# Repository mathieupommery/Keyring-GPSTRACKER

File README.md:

# Keyring-GPSTRACKER (v12.0)

<p align="center">
  <video src="https://github.com/user-attachments/assets/1a3d3f26-0a68-42e8-81eb-b6b98553143f" width="600" controls autoplay loop muted></video>
</p>

An ultra-compact, highly integrated modular GPS logger built around the STM32G0B1KE and a custom u-blox MIA-M10Q implementation. This project is designed as a fully functional, wearable GNSS tracker featuring worldwide offline geographical awareness, high-frequency SD card logging, Bluetooth connectivity, extreme power management (2µA shutdown draw), and modular waterproof enclosures.

## Key Features

* **Configurable High-Speed Logging:** Records tracks directly to the internal MicroSD card in `.GPX` or `.CSV` format. The logging frequency is adjustable, supporting real-time capture from **1Hz up to 10Hz**.
* **Worldwide Offline Awareness & Navigation:** Anywhere in the world, the device can instantly identify the closest city (name, direction, population) or the nearest mountain peak. It provides precise directional pointers by fusing data from the GPS, the MMC5603 compass, and the ICM-42688-P IMU.
* **Topological Barometer Calibration:** Future firmware implementation of an offline map of topological elevation points stored on the SD card, allowing ultra-precise, automatic recalibration of the barometer altitude.
* **BLE Smartphone Connectivity:** An external **DA14531 Bluetooth Low Energy (BLE)** module will handle seamless, low-power synchronization and configuration with a smartphone app.
* **Plug & Play USB:** Acts as a USB Mass Storage Class (MSC) over USB-C. Simply plug the tracker into a computer to access the MicroSD card and retrieve your tracks without removing the card.
* **Extreme Low Power:** Fully active power draw is around ~30mA. In shutdown mode, with only 1 LDO running for the STM32, the system draws just **2µA**.

---

## Modular Hardware Ecosystem (4 Custom PCBs)

The project relies on an ecosystem of four custom PCBs (two 6-layer boards and two 2-layer boards) connected via ultra-compact 5-pin board-to-board connectors.

### 1. Mainboard (6-Layer)
The core of the tracker, engineered to maximize available I/O ports while maintaining a tiny footprint.
* **MCU:** STM32G0B1KE (chosen for native USB FS 2.0, ultra-low power shutdown modes, and only 1 VDD pin).
* **Internal Sensors:** MMC5603 (compass), ICM-42688-P (IMU), and DPS368 (barometer).
* **Storage & Connectivity:** MicroSD card slot operating in SPI mode + external DA14531 BLE module support.
* **Power & Charging:** LTC4065 LiPo battery charger with USB-C connector.

#### BLE Expansion Module (DA14531)
To keep the mainboard ultra-compact while allowing wireless smartphone communication, wireless connectivity is offloaded to a dedicated mini extension PCB. Connected directly to the back of the mainboard via a board-to-board connector, this add-on integrates the ultra-low-power **Renesas DA14531 CodeLess BLE module**.

### 2. Custom GNSS Receiver Board (6-Layer)
A custom BGA adaptation of the u-blox **MIA-M10Q** receiver with a dedicated SAW filter and a top-mounted ceramic patch antenna. Designed as a footprint clone of the PA1010D, but utilizing a far superior engine capable of 10Hz updates across all constellations simultaneously.

### 3. Display & Waterproof Extension Panel (Breakaway 2-Layer PCB)

To optimize manufacturing, all auxiliary modules are designed as a single **snap-away (breakaway) panelized 2-layer PCB** so they can be produced together in one manufacturing run. Once snapped apart, the panel yields three distinct functional boards:

* **0.42" OLED Carrier Board:** Adapts a 0.42-inch SSD1306 OLED screen to the custom 5/6-pin board-to-board (B2B) connector format. It also breaks out the I2C bus to an external JST SM05B connector and includes an external GPIO breakout for a hardware button.
* **0.49" OLED Carrier Board:** Identical architecture to the 0.42" version (B2B adaptation, JST SM05B I2C breakout, button GPIO), but specifically dimensioned to mount a slightly larger 0.49-inch SSD1306 OLED screen.
* **Waterproof Dive Extension Board:** Designed specifically to mount inside the waterproof enclosure for deep-water excursions. It adds a **TE Connectivity 30-bar external pressure sensor** (effectively turning the tracker into a compact dive computer) and a magnetic **Hall-effect switch** for contactless power/stop-mode toggling through the solid sealed case.

## Smart Power Architecture

Power is cleanly isolated and distributed via 3 independent ultra-low IQ LDOs, controlled by the MCU:
* **LDO 1 (Always-on / MCU baseline):** Powers the STM32 directly. Responsible for the 2µA deep shutdown consumption.
* **LDO 2 (Switched):** Dedicated exclusively to the GNSS module.
* **LDO 3 (Switched):** Powers the SSD1306 display, the MicroSD card, external sensors (including the BLE module), and internal sensors.

---

## Enclosure System: Standard vs. Waterproof (Dive Mode)

The tracker features a modular, tool-free swap enclosure system depending on your activity:

### 1. Standard Compact Case
The daily-use enclosure. It is ultra-compact, non-waterproof, and provides direct access to the OLED display, physical buttons, MicroSD card slot, and USB-C port for charging and mass-storage data transfer.

### 2. Waterproof Dive Case
Similar to a GoPro housing, this heavy-duty case is designed for underwater excursions down to several hundred meters. 
* **How it works:** You remove the mainboard from the standard case, connect it to the **Waterproof Extension Board** (with the 30-bar sensor and Hall switch already mounted inside the dive case), turn it on, and seal the enclosure.
* **Note:** While in this temporary dive case, USB charging and physical MicroSD card access are blocked to ensure 100% water tightness. Power state is managed entirely through the external magnetic Hall sensor.

---

## Open Source

This project is fully open source! Feel free to explore the schematics, layouts, and firmware. If you find this project interesting or build your own, **please consider leaving a ⭐ on the repository!**

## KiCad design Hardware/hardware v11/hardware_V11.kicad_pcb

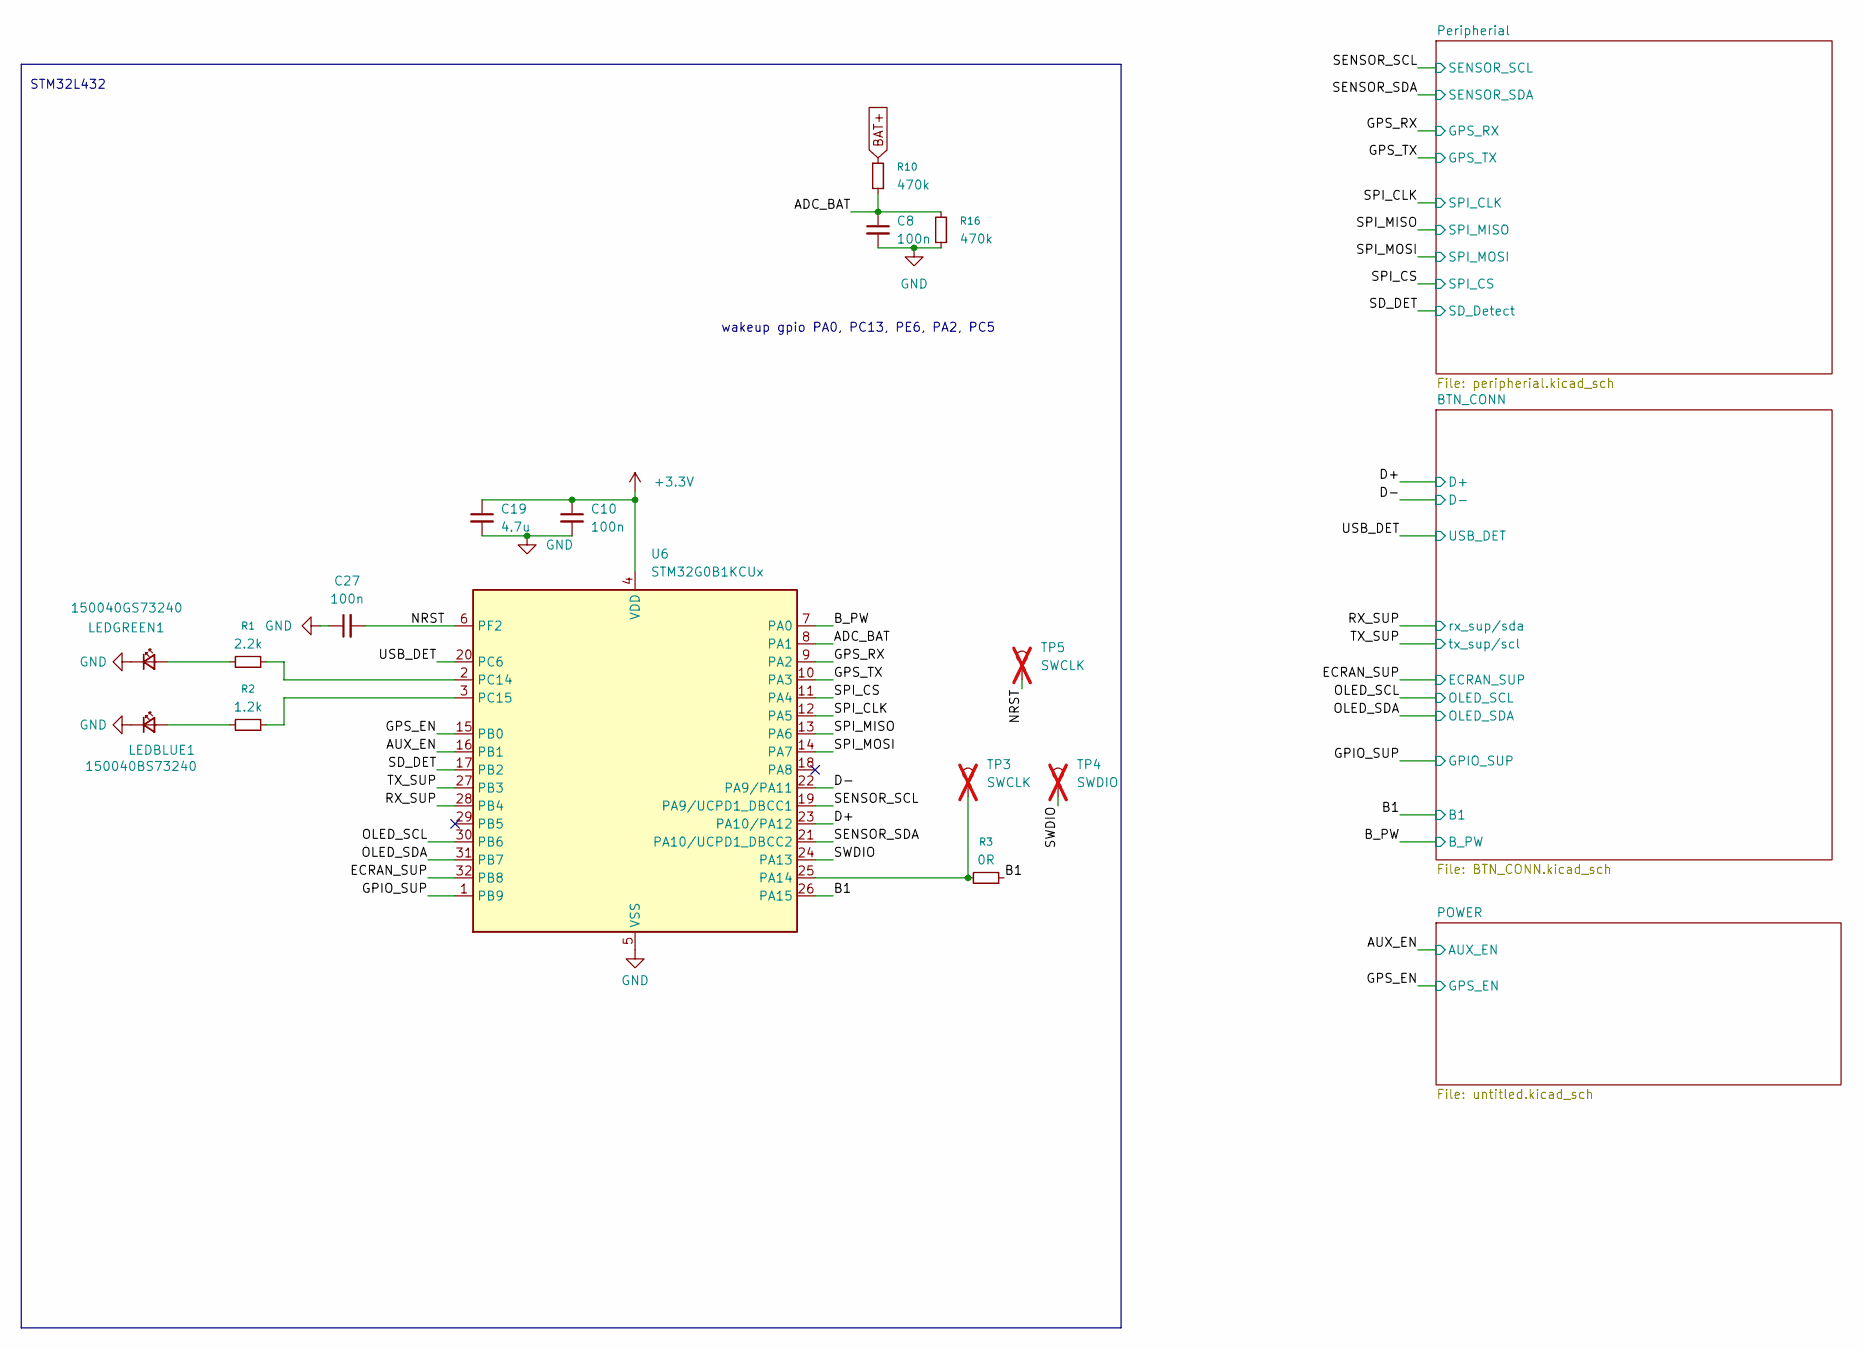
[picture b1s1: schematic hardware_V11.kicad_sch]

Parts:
C8, C10, C27: 100n; C_0201_0603Metric_Pad0.64x0.40mm_HandSolder
C19: 4.7u; C_0402_1005Metric
LEDBLUE1: 150040BS73240; LED_0402_1005Metric; Manufacturer_Part_Number 150040BS73240; Mouser Part Number 710-150040BS73240
LEDGREEN1: 150040GS73240; LED_0402_1005Metric; Manufacturer_Part_Number 150040GS73240; Mouser Part Number 710-150040GS73240
R1: 2.2k; R_0201_0603Metric_Pad0.64x0.40mm_HandSolder; Mouser Part Number 603-RC0201JR-07510RL
R2: 1.2k; R_0201_0603Metric_Pad0.64x0.40mm_HandSolder; Mouser Part Number 603-RC0201JR-07510RL
R3: 0R; R_0201_0603Metric_Pad0.64x0.40mm_HandSolder; Mouser Part Number 603-RC0201JR-07510RL
R10, R16: 470k; R_0201_0603Metric_Pad0.64x0.40mm_HandSolder; Mouser Part Number 603-AC0201FR-07470KL
TP3, TP5: SWCLK; pad_0.7mm; not fitted
TP4: SWDIO; pad_0.7mm; not fitted
U6: STM32G0B1KCUx; QFN-32-1EP_5x5mm_P0.5mm_EP3.45x3.45mm

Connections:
+3.3V: C10.1, C19.1, U6.4 (VDD); also elsewhere on the board
/ADC_BAT: C8.1, R10.2, R16.2, U6.8 (PA1)
/AUX_EN: U6.16 (PB1); also elsewhere on the board
/B1: R3.1, U6.26 (PA15); also elsewhere on the board
/B_PW: U6.7 (PA0); also elsewhere on the board
/D+: U6.23 (PA10/PA12); also elsewhere on the board
/D-: U6.22 (PA9/PA11); also elsewhere on the board
/ECRAN_SUP: U6.32 (PB8); also elsewhere on the board
/GPIO_SUP: U6.1 (PB9); also elsewhere on the board
/GPS_EN: U6.15 (PB0); also elsewhere on the board
/GPS_RX: U6.9 (PA2); also elsewhere on the board
/GPS_TX: U6.10 (PA3); also elsewhere on the board
/NRST: C27.2, TP5.1 (1_1), U6.6 (PF2)
/OLED_SCL: U6.30 (PB6); also elsewhere on the board
/OLED_SDA: U6.31 (PB7); also elsewhere on the board
/RX_SUP: U6.28 (PB4); also elsewhere on the board
/SD_DET: U6.17 (PB2); also elsewhere on the board
/SENSOR_SCL: U6.19 (PA9/UCPD1_DBCC1); also elsewhere on the board
/SENSOR_SDA: U6.21 (PA10/UCPD1_DBCC2); also elsewhere on the board
/SPI_CLK: U6.12 (PA5); also elsewhere on the board
/SPI_CS: U6.11 (PA4); also elsewhere on the board
/SPI_MISO: U6.13 (PA6); also elsewhere on the board
/SPI_MOSI: U6.14 (PA7); also elsewhere on the board
/SWDIO: TP4.1 (1_1), U6.24 (PA13)
/TX_SUP: U6.27 (PB3); also elsewhere on the board
/USB_DET: U6.20 (PC6); also elsewhere on the board
BAT+: R10.1; also elsewhere on the board
GND: C8.2, C10.2, C19.2, C27.1, LEDBLUE1.1 (K), LEDGREEN1.1 (K), R16.1, U6.5 (VSS), U6.33 (VSS); also elsewhere on the board
unnamed: LEDBLUE1.2 (A), R2.2
unnamed: LEDGREEN1.2 (A), R1.2
unnamed: R3.2, TP3.1 (1_1), U6.25 (PA14)
unnamed: R1.1, U6.2 (PC14)
unnamed: R2.1, U6.3 (PC15)

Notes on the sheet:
STM32L432
wakeup gpio PA0, PC13, PE6, PA2, PC5

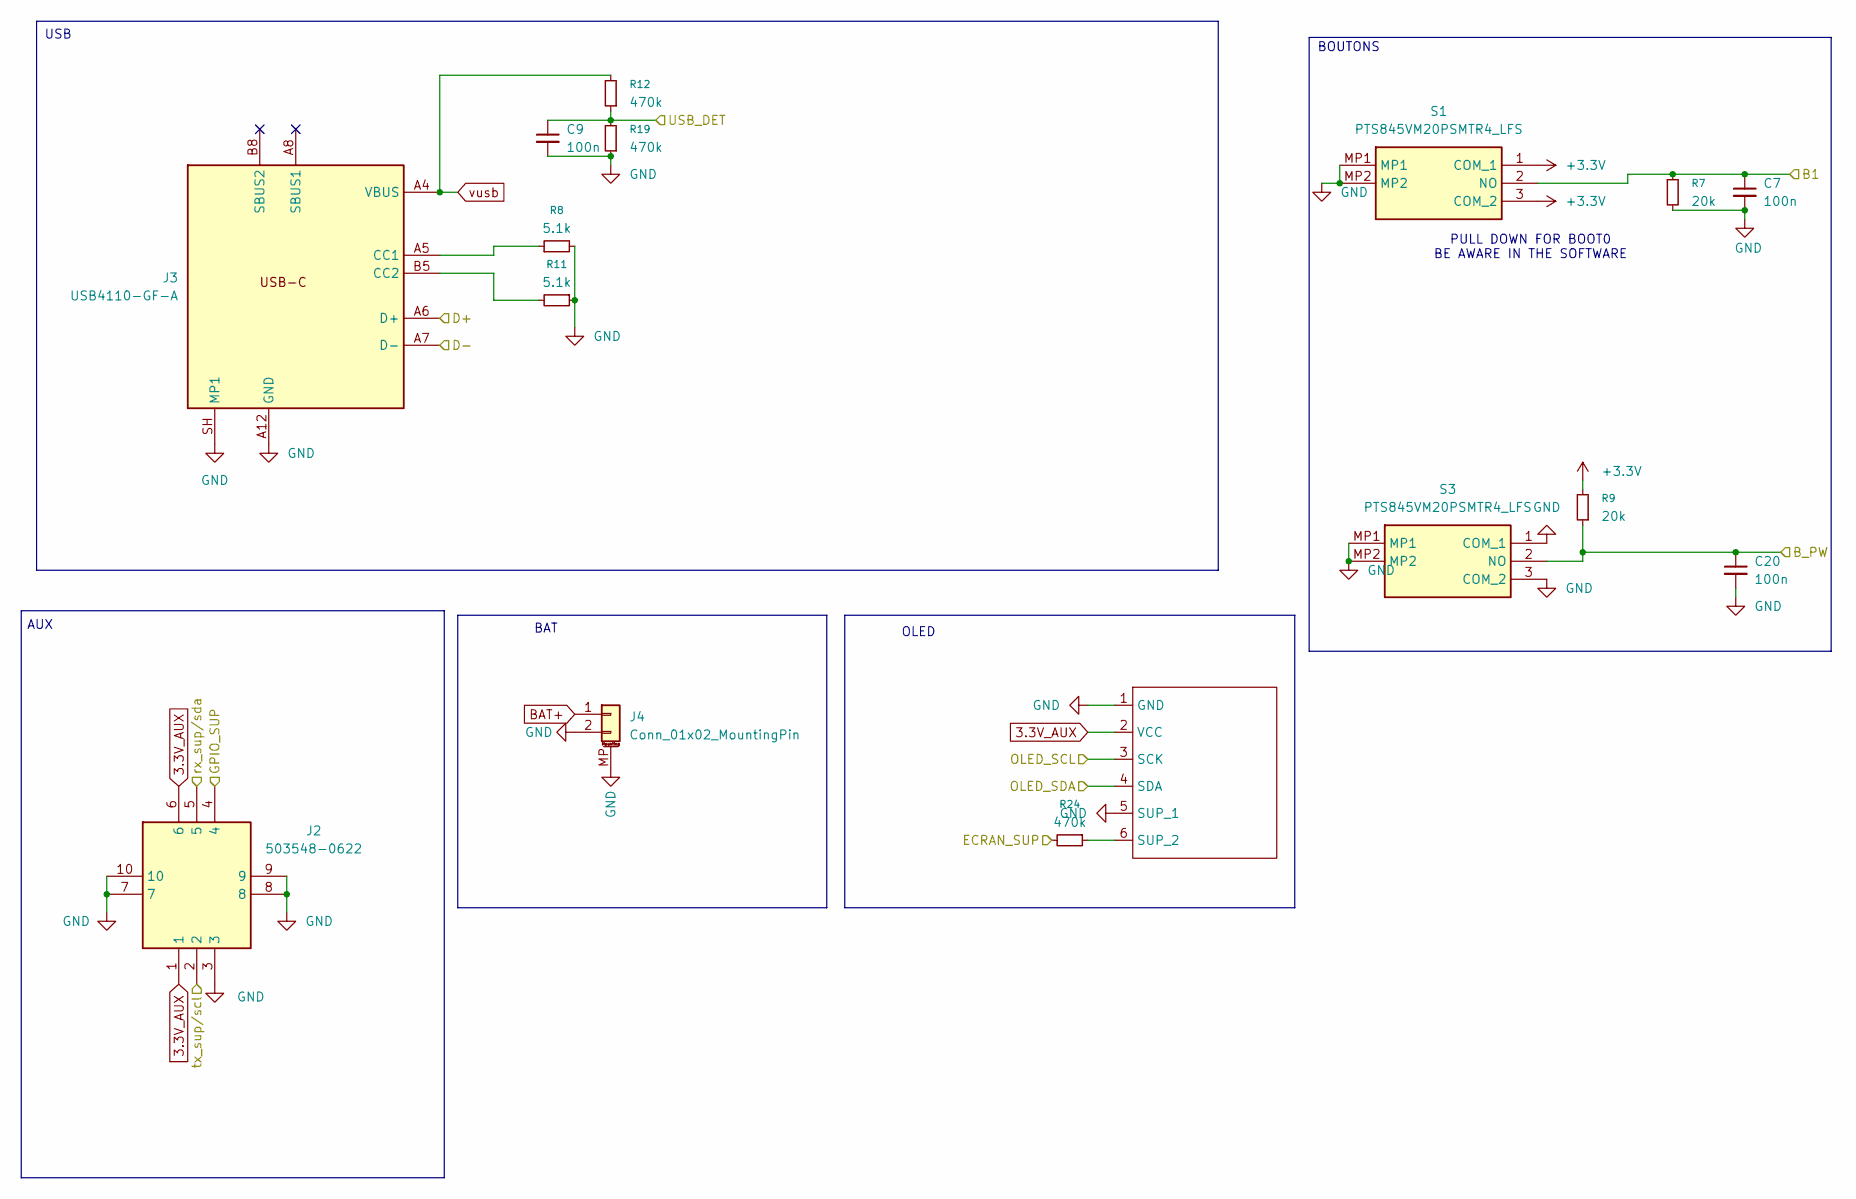
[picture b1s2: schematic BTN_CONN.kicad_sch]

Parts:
C7, C9, C20: 100n; C_0201_0603Metric_Pad0.64x0.40mm_HandSolder
J2: 503548-0622; 5035480622; Manufacturer_Part_Number 503548-0622; Mouser Part Number 538-503548-0622
J3: USB4110-GF-A; USB_C_Receptacle_GCT_USB4105-xx-A_16P_TopMnt_Horizontal; Mouser Part Number 640-USB4110-GF-A
J4: Conn_01x02_MountingPin; JST_SUR_BM02B-SURS-TF_1x02-1MP_P0.80mm_Vertical
R7, R9: 20k; R_0201_0603Metric_Pad0.64x0.40mm_HandSolder; Mouser Part Number 603-AC0201FR-0720KL
R8, R11: 5.1k; R_0201_0603Metric_Pad0.64x0.40mm_HandSolder; Mouser Part Number 603-AC0201FR-0720KL
R12, R19, R24: 470k; R_0201_0603Metric_Pad0.64x0.40mm_HandSolder; Mouser Part Number 603-AC0201FR-0720KL
S1, S3: PTS845VM20PSMTR4_LFS; PTS845VM20PSMTR4LFS; Manufacturer_Part_Number PTS845VM20PSMTR4 LFS; Mouser Part Number 611-PTS845VM20PSMTR4
U4: ssd1306_5point

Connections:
3.3V_AUX: J2.1, J2.6, U4.2 (VCC); also elsewhere on the board
+3.3V: R9.2, S1.1 (COM_1), S1.3 (COM_2); also elsewhere on the board
/B1: C7.1, R7.1, S1.2 (NO); also elsewhere on the board
/B_PW: C20.1, R9.1, S3.2 (NO); also elsewhere on the board
/D+: J3.A6 (D+), J3.B6 (D+); also elsewhere on the board
/D-: J3.A7 (D-), J3.B7 (D-); also elsewhere on the board
/ECRAN_SUP: R24.2; also elsewhere on the board
/GPIO_SUP: J2.4; also elsewhere on the board
/OLED_SCL: U4.3 (SCK); also elsewhere on the board
/OLED_SDA: U4.4 (SDA); also elsewhere on the board
/RX_SUP: J2.5; also elsewhere on the board
/TX_SUP: J2.2; also elsewhere on the board
/USB_DET: C9.1, R12.1, R19.2; also elsewhere on the board
BAT+: J4.1; also elsewhere on the board
GND: C7.2, C9.2, C20.2, J2.3, J2.7, J2.8, J2.9, J2.10, J3.A1 (GND), J3.A12 (GND), J3.B1 (GND), J3.B12 (GND), J3.SH (MP1), J4.2, J4.MP (MountPin), R7.2, R8.2, R11.1, R19.1, S1.MP1, S1.MP2, S3.1 (COM_1), S3.3 (COM_2), S3.MP1, S3.MP2, U4.1 (GND), U4.5 (SUP_1); also elsewhere on the board
unnamed: J3.A5 (CC1), R8.1
unnamed: J3.B5 (CC2), R11.2
unnamed: R24.1, U4.6 (SUP_2)
vusb: J3.A4 (VBUS), J3.A9 (VBUS), J3.B4 (VBUS), J3.B9 (VBUS), R12.2; also elsewhere on the board

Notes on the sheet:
AUX
BOUTONS
USB
PULL DOWN FOR BOOT0 BE AWARE IN THE SOFTWARE
OLED
BAT

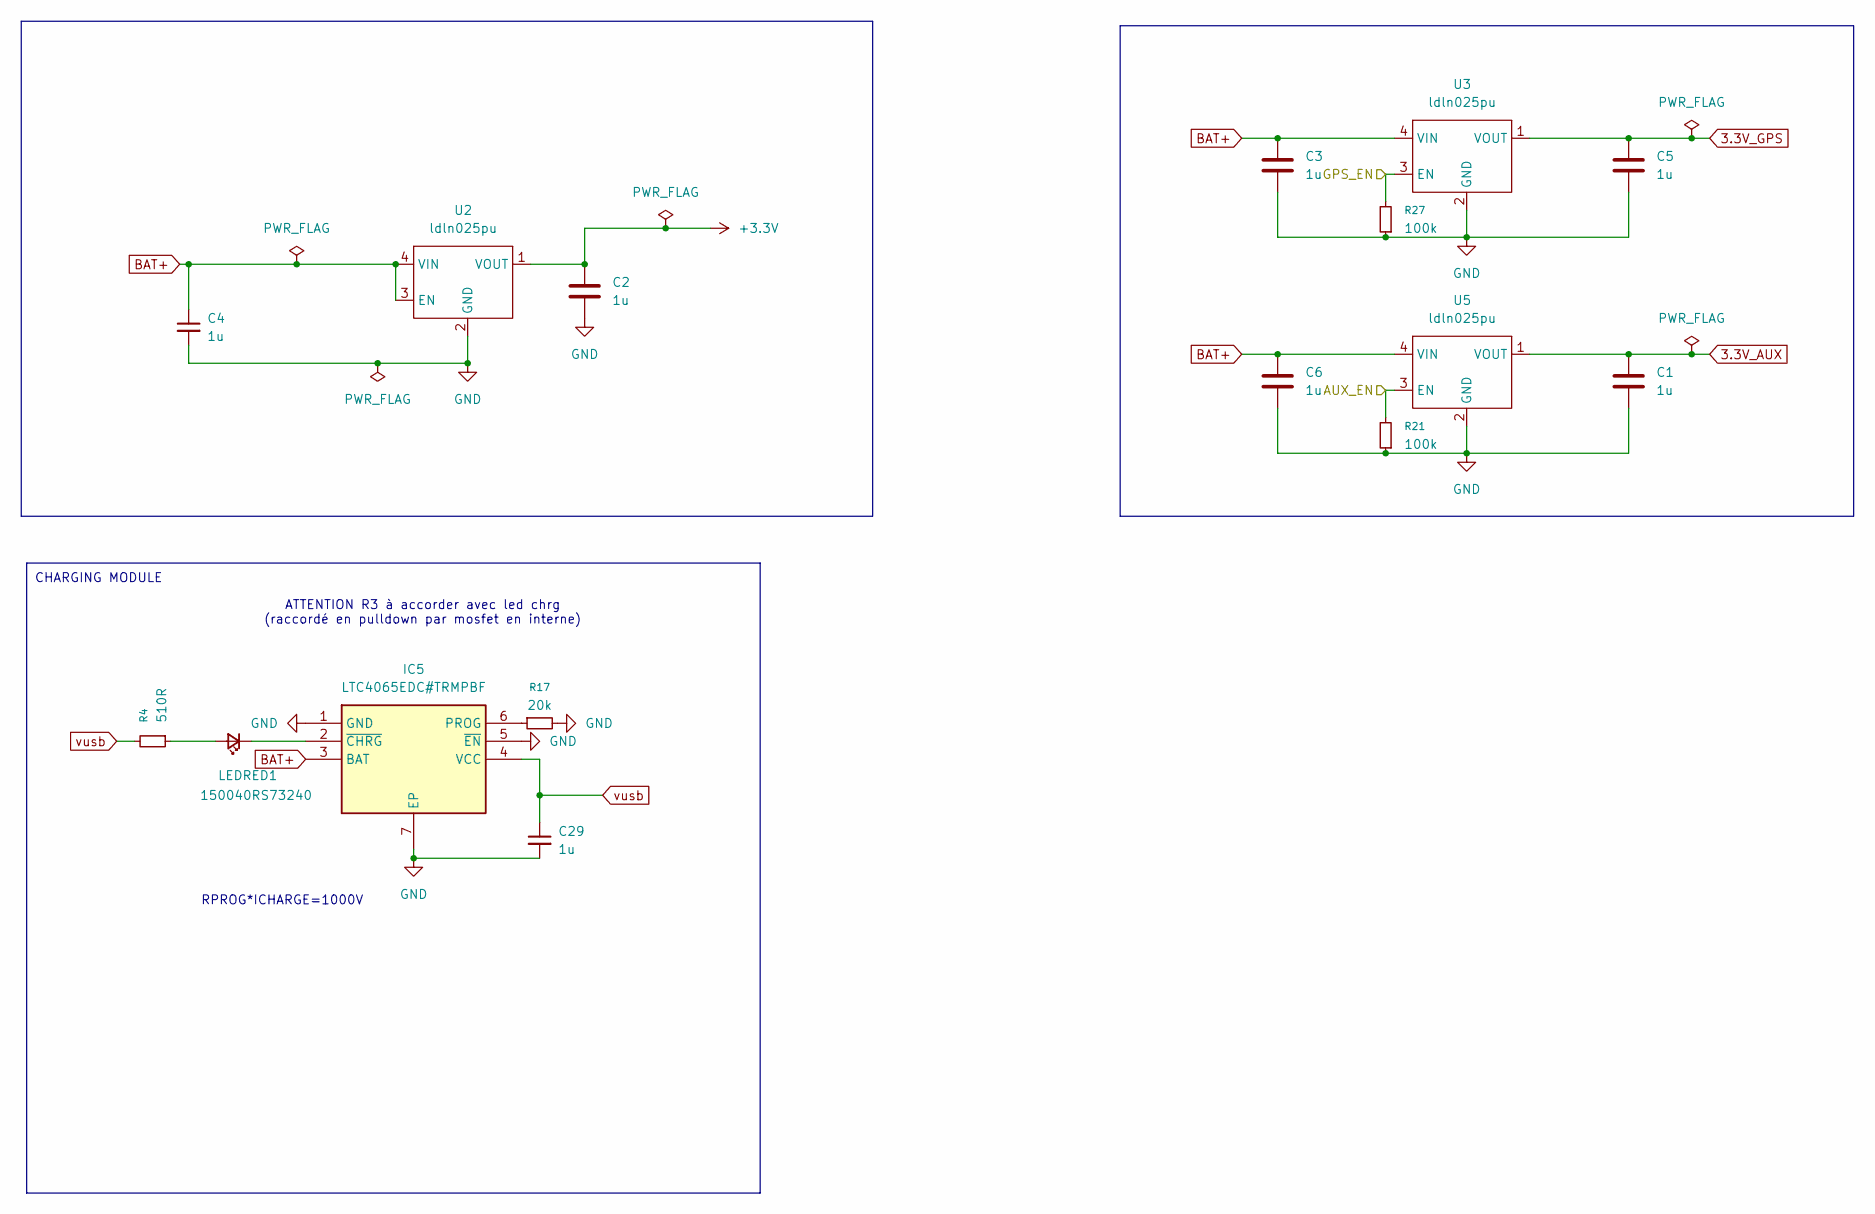
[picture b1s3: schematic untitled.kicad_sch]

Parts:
C1, C2, C3, C4, C5, C6, C29: 1u; C_0201_0603Metric_Pad0.64x0.40mm_HandSolder
IC5: LTC4065EDC#TRMPBF; SON50P200X200X80-7N-D; Manufacturer_Part_Number LTC4065EDC#TRMPBF; Mouser Part Number 584-LTC4065EDCTRMPBF
LEDRED1: 150040RS73240; LED_0402_1005Metric; Manufacturer_Part_Number 150040GS73240; Mouser Part Number 710-150040GS73240
R4: 510R; R_0201_0603Metric_Pad0.64x0.40mm_HandSolder; Mouser Part Number 603-RC0201JR-07510RL
R17: 20k; R_0201_0603Metric_Pad0.64x0.40mm_HandSolder; Mouser Part Number 603-AC0201FR-0720KL
R21, R27: 100k; R_0201_0603Metric_Pad0.64x0.40mm_HandSolder; Mouser Part Number 603-RC0201BR-07100KL
U2, U3, U5: ldln025pu; Mouser Part Number 511-LDLN025PU33R

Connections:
3.3V_AUX: C1.1, U5.1 (VOUT); also elsewhere on the board
3.3V_GPS: C5.1, U3.1 (VOUT); also elsewhere on the board
+3.3V: C2.1, U2.1 (VOUT); also elsewhere on the board
/AUX_EN: R21.2, U5.3 (EN); also elsewhere on the board
/GPS_EN: R27.2, U3.3 (EN); also elsewhere on the board
BAT+: C3.1, C4.1, C6.1, IC5.3 (BAT), U2.3 (EN), U2.4 (VIN), U3.4 (VIN), U5.4 (VIN); also elsewhere on the board
GND: C1.2, C2.2, C3.2, C4.2, C5.2, C6.2, C29.2, IC5.1 (GND), IC5.5 (~EN), IC5.7 (EP), R17.2, R21.1, R27.1, U2.2 (GND), U3.2 (GND), U5.2 (GND); also elsewhere on the board
unnamed: IC5.6 (PROG), R17.1
unnamed: IC5.2 (~CHRG), LEDRED1.1 (K)
unnamed: LEDRED1.2 (A), R4.1
vusb: C29.1, IC5.4 (VCC), R4.2; also elsewhere on the board

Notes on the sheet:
RPROG*ICHARGE=1000V
ATTENTION R3 à accorder avec led chrg (raccordé en pulldown par mosfet en interne)
CHARGING MODULE

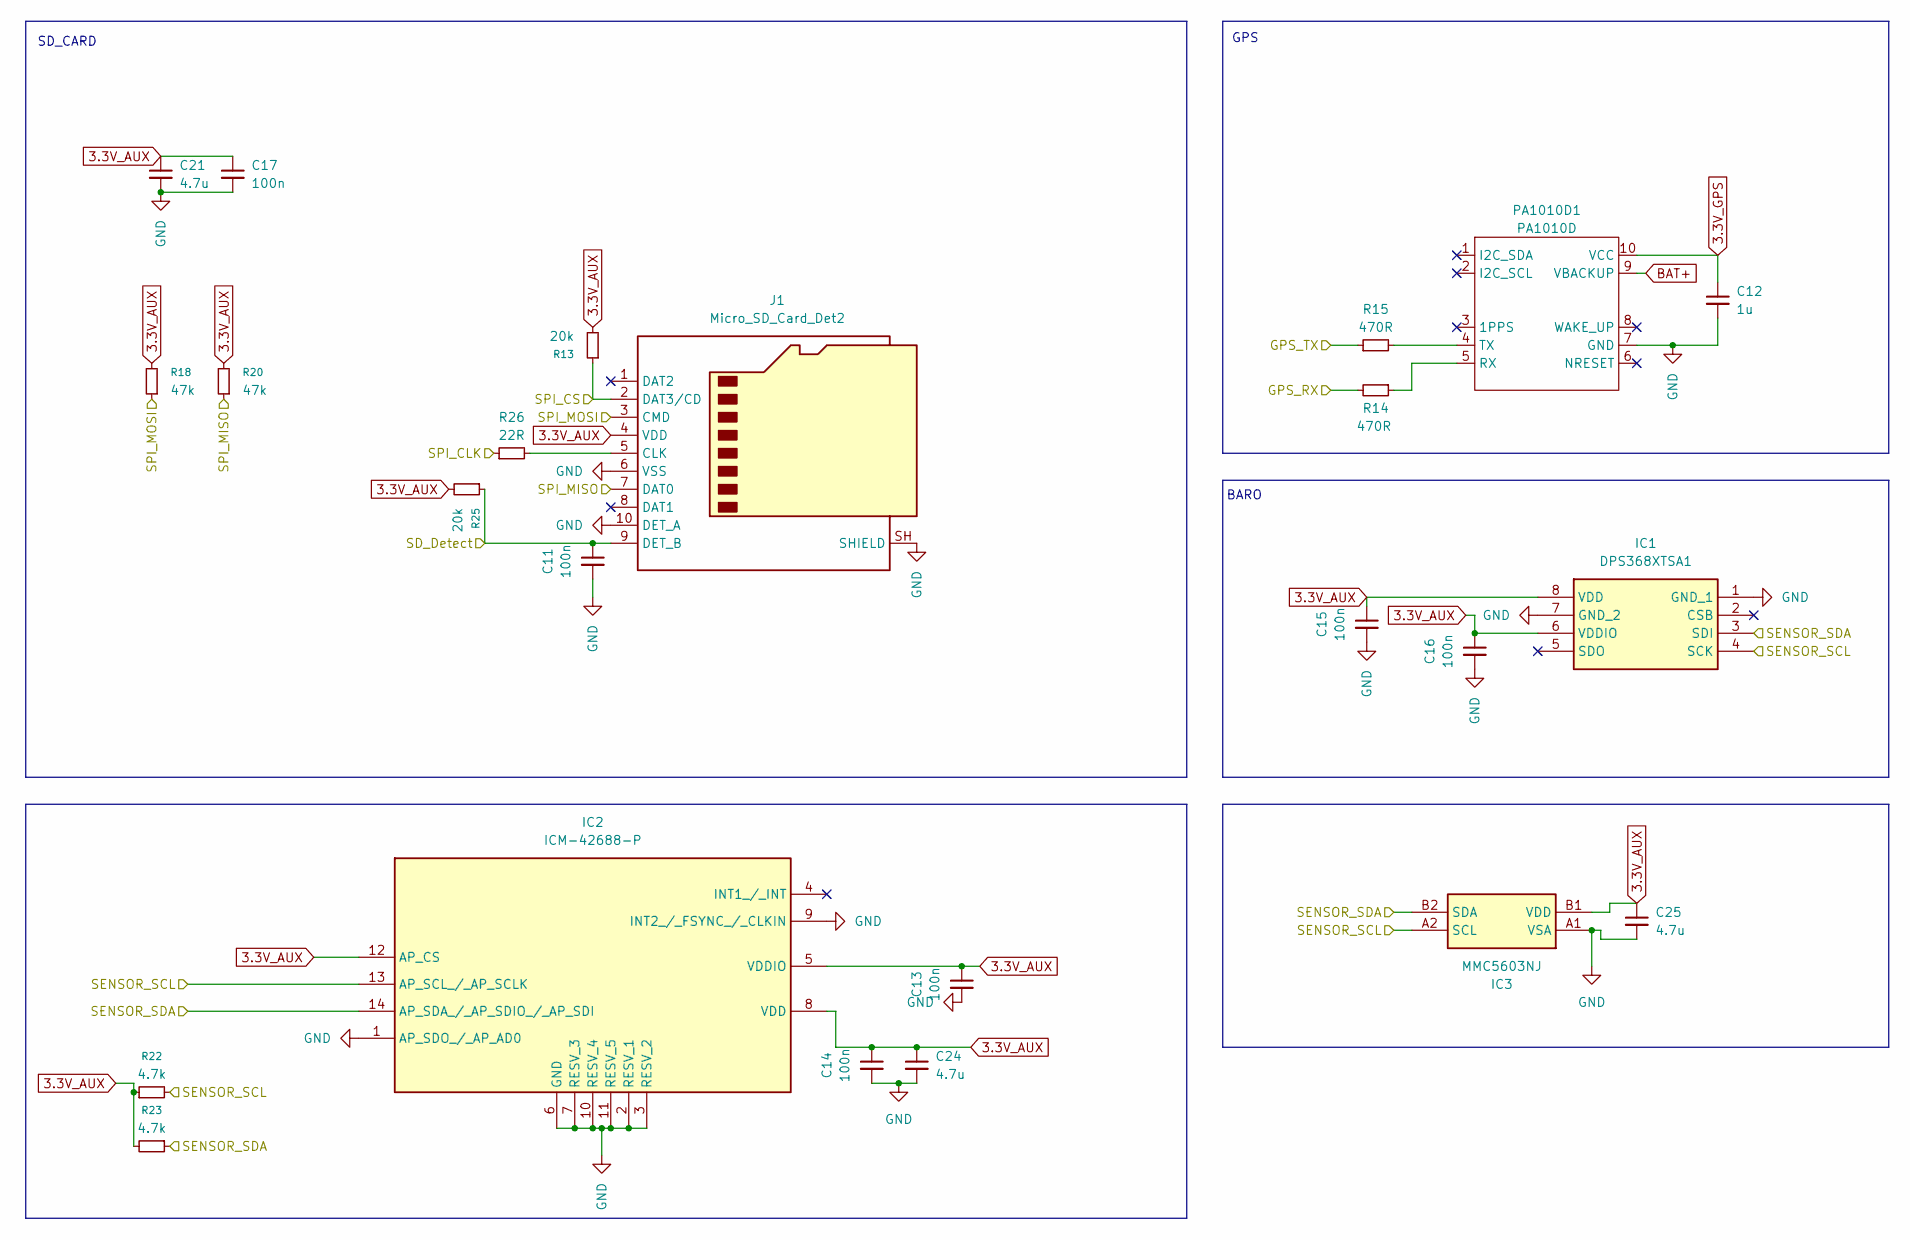
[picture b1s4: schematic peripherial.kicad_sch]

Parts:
C11, C13, C14, C15, C16, C17: 100n; C_0201_0603Metric_Pad0.64x0.40mm_HandSolder
C12: 1u; C_0201_0603Metric_Pad0.64x0.40mm_HandSolder
C21, C24, C25: 4.7u; C_0402_1005Metric
IC1: DPS368XTSA1; Mouser Part Number 726-DPS368XTSA1
IC2: ICM-42688-P; IIM42352; Manufacturer_Part_Number ICM-42688-P; Mouser Part Number 410-ICM-42688-P
IC3: MMC5603NJ; Manufacturer_Part_Number MMC5603NJ; Mouser Part Number 438-MMC5603NJ
J1: Micro_SD_Card_Det2; microSD_HC_Molex_104031-0811
PA1010D1: PA1010D
R13, R25: 20k; R_0201_0603Metric_Pad0.64x0.40mm_HandSolder; Mouser Part Number 603-AC0201FR-0720KL
R14, R15: 470R; R_0201_0603Metric_Pad0.64x0.40mm_HandSolder
R18, R20: 47k; R_0201_0603Metric_Pad0.64x0.40mm_HandSolder; Mouser Part Number 603-AC0201FR-0720KL
R22, R23: 4.7k; R_0201_0603Metric_Pad0.64x0.40mm_HandSolder; Mouser Part Number 603-AC0201FR-0720KL
R26: 22R; R_0201_0603Metric_Pad0.64x0.40mm_HandSolder

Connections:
3.3V_AUX: C13.1, C14.1, C15.1, C16.1, C17.1, C21.1, C24.1, C25.1, IC1.6 (VDDIO), IC1.8 (VDD), IC2.5 (VDDIO), IC2.8 (VDD), IC2.12 (AP_CS), IC3.B1 (VDD), J1.4 (VDD), R13.2, R18.2, R20.2, R22.1, R23.2, R25.2; also elsewhere on the board
3.3V_GPS: C12.1, PA1010D1.10 (VCC); also elsewhere on the board
/GPS_RX: R14.2; also elsewhere on the board
/GPS_TX: R15.1; also elsewhere on the board
/SD_DET: C11.1, J1.9 (DET_B), R25.1; also elsewhere on the board
/SENSOR_SCL: IC1.4 (SCK), IC2.13 (AP_SCL_/_AP_SCLK), IC3.A2 (SCL), R22.2; also elsewhere on the board
/SENSOR_SDA: IC1.3 (SDI), IC2.14 (AP_SDA_/_AP_SDIO_/_AP_SDI), IC3.B2 (SDA), R23.1; also elsewhere on the board
/SPI_CLK: R26.1; also elsewhere on the board
/SPI_CS: J1.2 (DAT3/CD), R13.1; also elsewhere on the board
/SPI_MISO: J1.7 (DAT0), R20.1; also elsewhere on the board
/SPI_MOSI: J1.3 (CMD), R18.1; also elsewhere on the board
BAT+: PA1010D1.9 (VBACKUP); also elsewhere on the board
GND: C11.2, C12.2, C13.2, C14.2, C15.2, C16.2, C17.2, C21.2, C24.2, C25.2, IC1.1 (GND_1), IC1.7 (GND_2), IC2.1 (AP_SDO_/_AP_AD0), IC2.2 (RESV_1), IC2.3 (RESV_2), IC2.6 (GND), IC2.7 (RESV_3), IC2.9 (INT2_/_FSYNC_/_CLKIN), IC2.10 (RESV_4), IC2.11 (RESV_5), IC3.A1 (VSA), J1.6 (VSS), J1.10 (DET_A), J1.SH (SHIELD), PA1010D1.7 (GND); also elsewhere on the board
unnamed: J1.5 (CLK), R26.2
unnamed: PA1010D1.5 (RX), R14.1
unnamed: PA1010D1.4 (TX), R15.2

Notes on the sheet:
SD_CARD
BARO
GPS

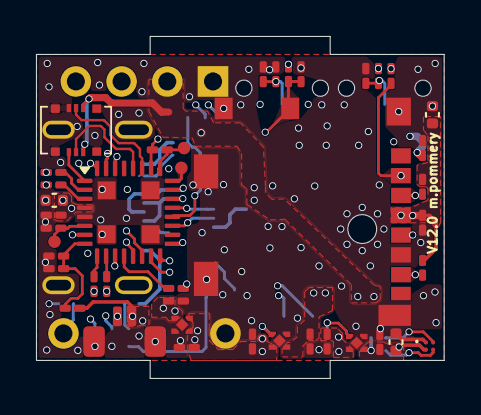
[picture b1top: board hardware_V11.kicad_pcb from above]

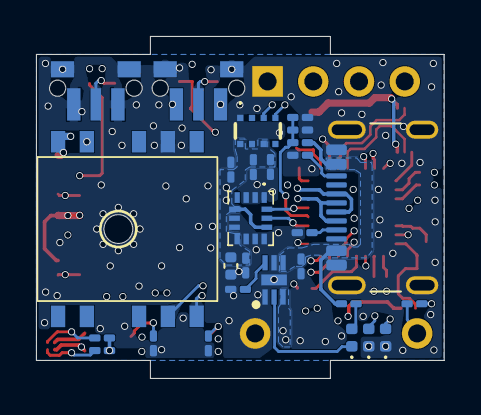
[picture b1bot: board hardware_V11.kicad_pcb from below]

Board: 6 copper layers, 22.7 x 19.0 mm, 71 parts (29 on the bottom side), 45 nets.

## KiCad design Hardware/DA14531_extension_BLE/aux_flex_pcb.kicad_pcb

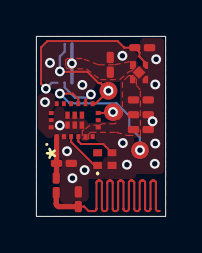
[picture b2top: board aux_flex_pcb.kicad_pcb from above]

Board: 2 copper layers, 7.2 x 10.0 mm, 15 parts (1 on the bottom side), 11 nets.

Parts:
C21, C26, C27: 1u; C_0201_0603Metric_Pad0.64x0.40mm_HandSolder
C22, C23: 3.3nF; C_0201_0603Metric_Pad0.64x0.40mm_HandSolder
C25: 100n; C_0201_0603Metric_Pad0.64x0.40mm_HandSolder
J4: 503552-0622; 5035520622
L2: 1.8nH; L_0201_0603Metric_Pad0.64x0.40mm_HandSolder
R22: 100k; R_0201_0603Metric_Pad0.64x0.40mm_HandSolder
TP6: swdio; 1mm_circle
TP7: swclk; 1mm_circle
TP8: rst; 1mm_circle
U1: ldln025pu
U2: DA14531-00000FX2; FCGQFN24_2.2X3.0_REN
Y1: 830108254201

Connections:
3.3V_AUX: C27.1, J4.1, J4.6, U1.4 (VIN)
/RF: C22.1, L2.1, U2.1 (RFIOp)
/SWCLK: TP7.1 (1_1), U2.12 (P0_2)
/SWDIO: TP6.1 (1_1), U2.9 (P0_10)
/exti: J4.3, R22.2, U1.3 (EN)
/rx_sup: J4.5, TP8.1 (1_1), U2.10 (RST/P0_0)
/tx_sup: J4.2, U2.11 (P0_1)
GND: C21.2, C22.2, C23.2, C25.2, C26.2, C27.2, J4.4, J4.MP1, J4.MP2, J4.MP3, J4.MP4, R22.1, U1.2 (GND), U2.2 (GNDRF2), U2.18 (RFIOm), U2.19 (GNDRF1), U2.20 (GND), U2.21 (GND_DCDC), U2.23 (VSS), Y1.2 (GND(LID))
unnamed: C21.1, C25.1, C26.1, U1.1 (VOUT), U2.5 (VBAT_LOW), U2.7 (VBAT_HIGH)
unnamed: U2.4 (XTAL32Mm), Y1.3 (CRYSTAL_2)
unnamed: U2.3 (XTAL32Mp), Y1.1 (CRYSTAL_1)

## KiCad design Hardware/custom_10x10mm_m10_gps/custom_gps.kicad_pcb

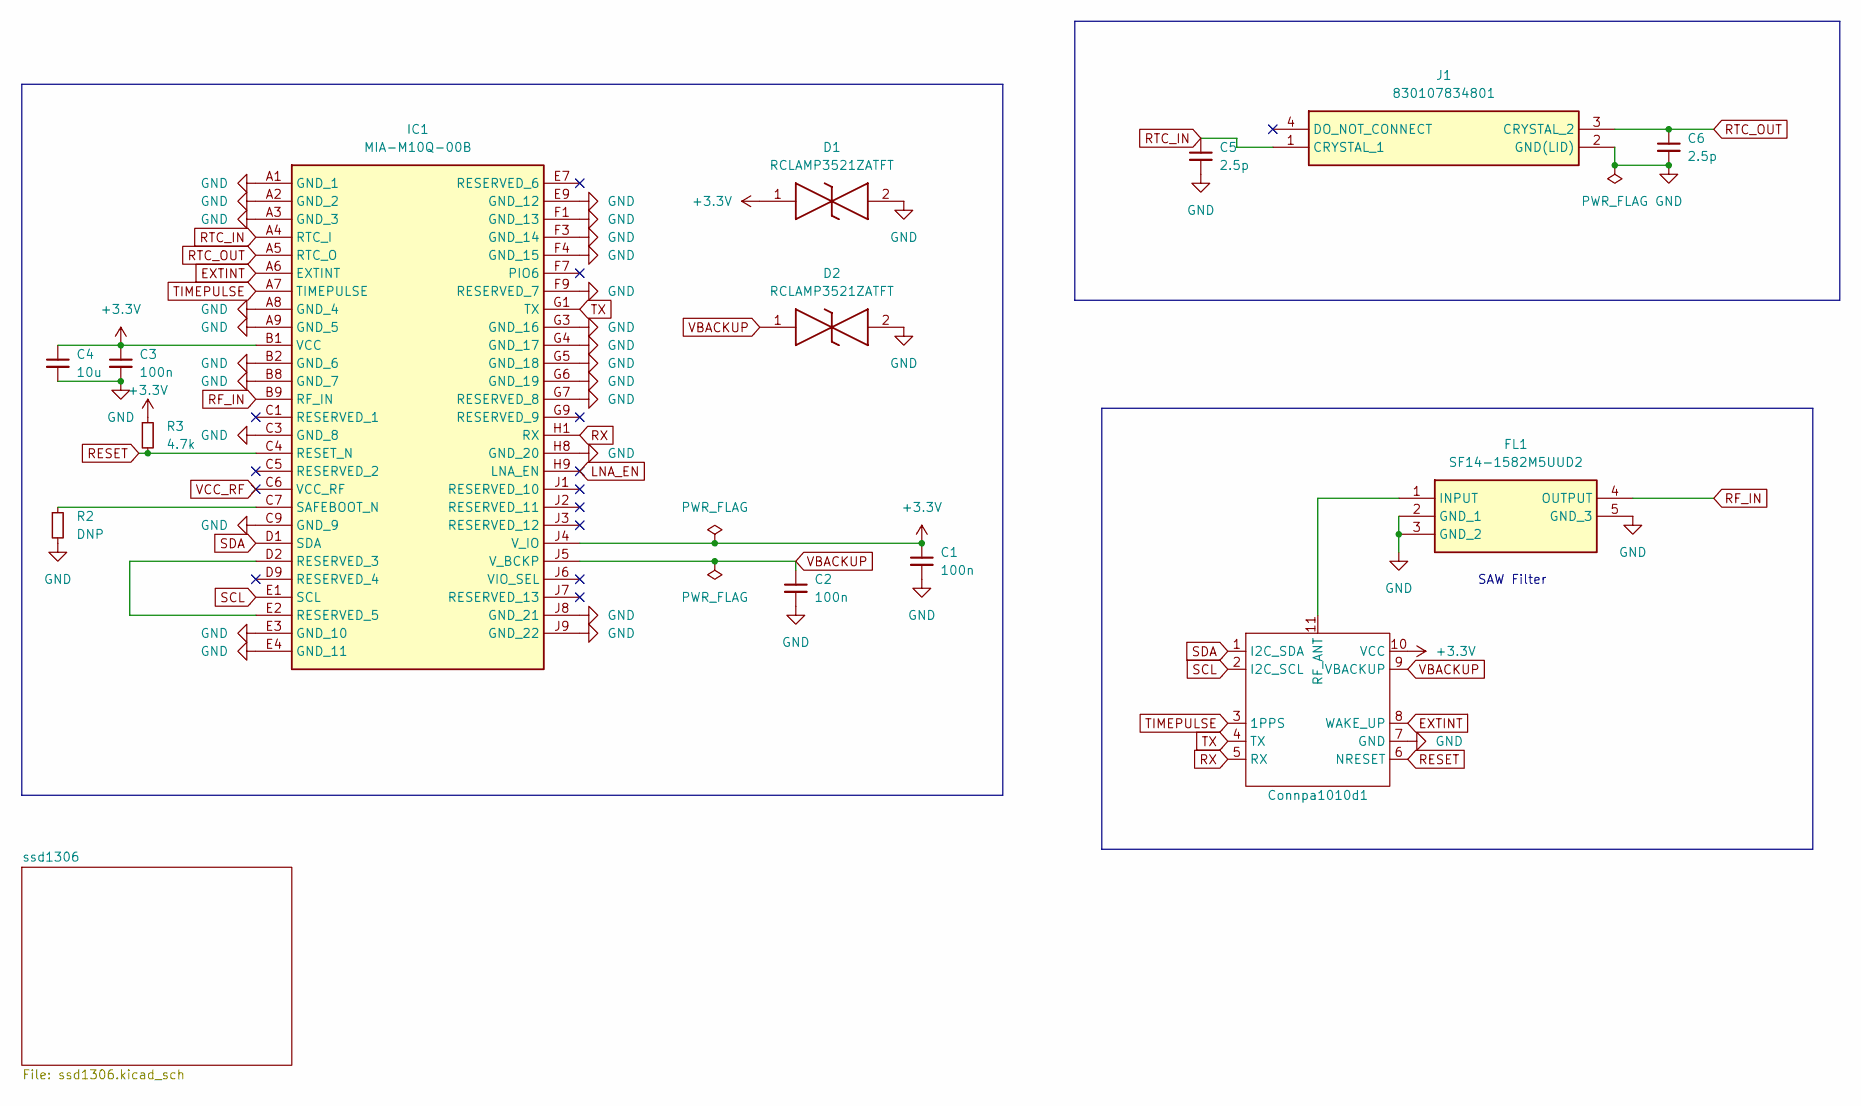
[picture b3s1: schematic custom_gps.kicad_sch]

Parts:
C1, C2, C3: 100n; C_0201_0603Metric
C4: 10u; C_0402_1005Metric
C5, C6: 2.5p; C_0201_0603Metric
Connpa1010d1: PA1010D
D1, D2: RCLAMP3521ZATFT; Mouser Part Number 947-RCLAMP3521ZATFT
FL1: SF14-1582M5UUD2; SF141582M5UUD2; Mouser Part Number 581-SF14-1582M5UUD2
IC1: MIA-M10Q-00B; MIAM10Q00B; Mouser Part Number 377-MIA-M10Q-00B
J1: 830107834801; Mouser Part Number 710-830107834801
R2: DNP; R_0201_0603Metric
R3: 4.7k; R_0201_0603Metric

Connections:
+3.3V: C1.1, C3.1, C4.1, Connpa1010d1.10 (VCC), D1.1, IC1.B1 (VCC), IC1.J4 (V_IO), R3.1
EXTINT: Connpa1010d1.8 (WAKE_UP), IC1.A6 (EXTINT)
GND: C1.2, C2.2, C3.2, C4.2, C5.2, C6.2, Connpa1010d1.7 (GND), D1.2, D2.2, FL1.2 (GND_1), FL1.3 (GND_2), FL1.5 (GND_3), IC1.A1 (GND_1), IC1.A2 (GND_2), IC1.A3 (GND_3), IC1.A8 (GND_4), IC1.A9 (GND_5), IC1.B2 (GND_6), IC1.B8 (GND_7), IC1.C3 (GND_8), IC1.C9 (GND_9), IC1.E3 (GND_10), IC1.E4 (GND_11), IC1.E9 (GND_12), IC1.F1 (GND_13), IC1.F3 (GND_14), IC1.F4 (GND_15), IC1.F9 (RESERVED_7), IC1.G3 (GND_16), IC1.G4 (GND_17), IC1.G5 (GND_18), IC1.G6 (GND_19), IC1.G7 (RESERVED_8), IC1.H8 (GND_20), IC1.J8 (GND_21), IC1.J9 (GND_22), J1.2 (GND(LID)), R2.2
LNA_EN: IC1.H9 (LNA_EN)
unnamed: Connpa1010d1.11 (RF_ANT), FL1.1 (INPUT)
unnamed: IC1.D2 (RESERVED_3), IC1.E2 (RESERVED_5)
unnamed: IC1.C7 (SAFEBOOT_N), R2.1
RESET: Connpa1010d1.6 (NRESET), IC1.C4 (RESET_N), R3.2
RF_IN: FL1.4 (OUTPUT), IC1.B9 (RF_IN)
RTC_IN: C5.1, IC1.A4 (RTC_I), J1.1 (CRYSTAL_1)
RTC_OUT: C6.1, IC1.A5 (RTC_O), J1.3 (CRYSTAL_2)
RX: Connpa1010d1.5 (RX), IC1.H1 (RX)
SCL: Connpa1010d1.2 (I2C_SCL), IC1.E1 (SCL)
SDA: Connpa1010d1.1 (I2C_SDA), IC1.D1 (SDA)
TIMEPULSE: Connpa1010d1.3 (1PPS), IC1.A7 (TIMEPULSE)
TX: Connpa1010d1.4 (TX), IC1.G1 (TX)
VBACKUP: C2.1, Connpa1010d1.9 (VBACKUP), D2.1, IC1.J5 (V_BCKP)
VCC_RF: IC1.C6 (VCC_RF)

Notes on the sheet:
SAW Filter

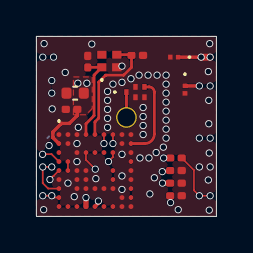
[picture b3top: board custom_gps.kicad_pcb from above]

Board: 6 copper layers, 10.0 x 10.0 mm, 14 parts (1 on the bottom side), 16 nets.

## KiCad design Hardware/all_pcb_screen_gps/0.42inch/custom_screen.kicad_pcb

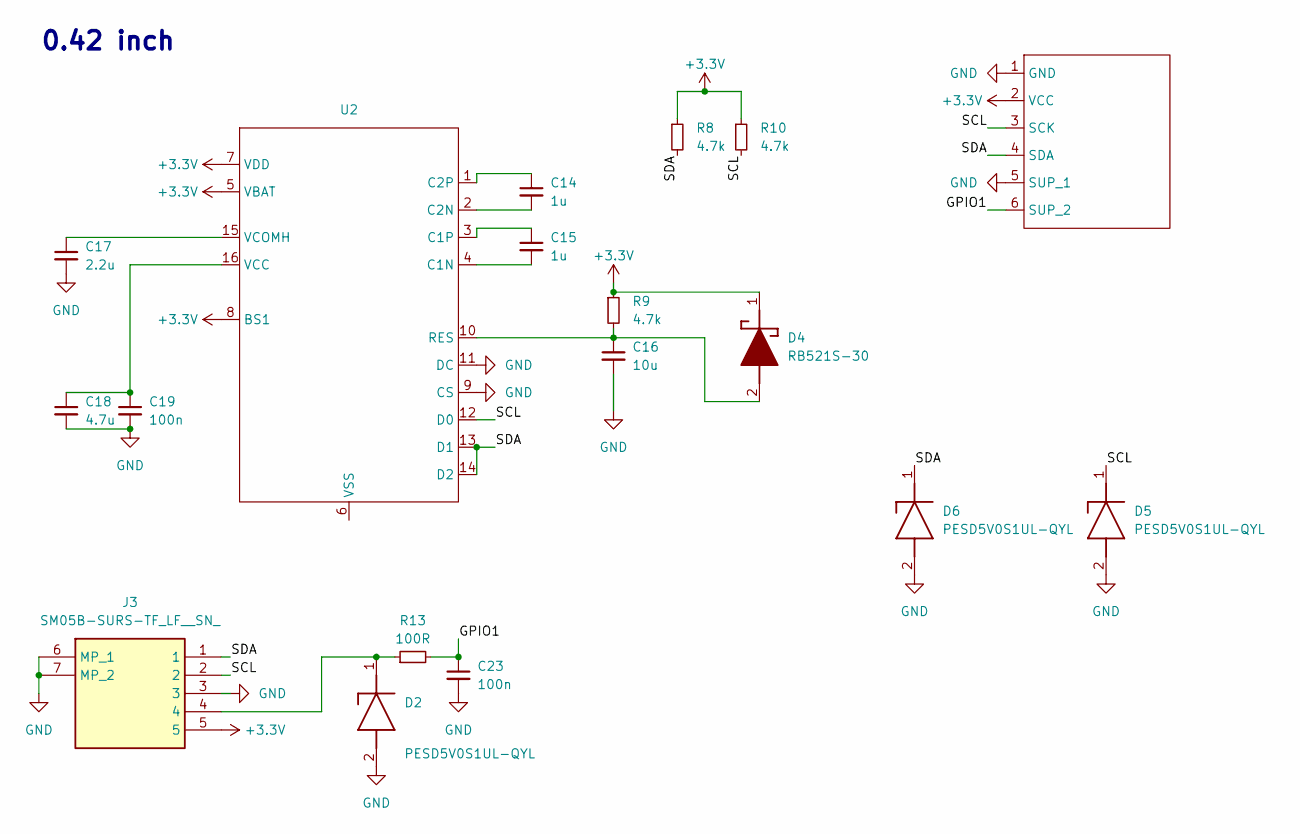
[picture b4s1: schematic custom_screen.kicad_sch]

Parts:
C14, C15: 1u; C_0201_0603Metric
C16: 10u; C_0402_1005Metric
C17: 2.2u; C_0402_1005Metric
C18: 4.7u; C_0402_1005Metric
C19, C23: 100n; C_0201_0603Metric
D2, D5, D6: PESD5V0S1UL-QYL; PESD5V0S1ULQYL; Manufacturer_Part_Number PESD5V0S1UL-QYL; Mouser Part Number 771-PESD5V0S1UL-QYL
D4: RB521S-30; SODFL1608X70N; Manufacturer_Part_Number RB521S-30
J3: SM05B-SURS-TF_LF__SN_; SM05BSURSTFLFSN; Manufacturer_Part_Number SM05B-SURS-TF(LF)(SN); Mouser Part Number 306-SM05BSURSTFLFSN
R8, R9, R10: 4.7k; R_0201_0603Metric
R13: 100R; R_0201_0603Metric
U2: ssd1306_0.42_fpc
U5: ssd1306_5point

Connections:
+3.3V: D4.1 (K), J3.5, R8.1, R9.1, R10.1, U2.5 (VBAT), U2.7 (VDD), U2.8 (BS1), U5.2 (VCC)
/GPIO1: C23.1, R13.2, U5.6 (SUP_2)
/SCL: D5.1 (K), J3.2, R10.2, U2.12 (D0), U5.3 (SCK)
/SDA: D6.1 (K), J3.1, R8.2, U2.13 (D1), U2.14 (D2), U5.4 (SDA)
GND: C16.2, C17.2, C18.2, C19.2, C23.2, D2.2 (A), D5.2 (A), D6.2 (A), J3.3, J3.6 (MP_1), J3.7 (MP_2), U2.9 (CS), U2.11 (DC), U5.1 (GND), U5.5 (SUP_1)
unnamed: D2.1 (K), J3.4, R13.1
unnamed: C16.1, D4.2 (A), R9.2, U2.10 (RES)
unnamed: C15.2, U2.4 (C1N)
unnamed: C15.1, U2.3 (C1P)
unnamed: C14.2, U2.2 (C2N)
unnamed: C14.1, U2.1 (C2P)
unnamed: C18.1, C19.1, U2.16 (VCC)
unnamed: C17.1, U2.15 (VCOMH)

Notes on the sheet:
0.42 inch
